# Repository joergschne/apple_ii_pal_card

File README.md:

# apple_ii_pal_card
 Apple II PAL Card - reloaded

APPLE II forever!

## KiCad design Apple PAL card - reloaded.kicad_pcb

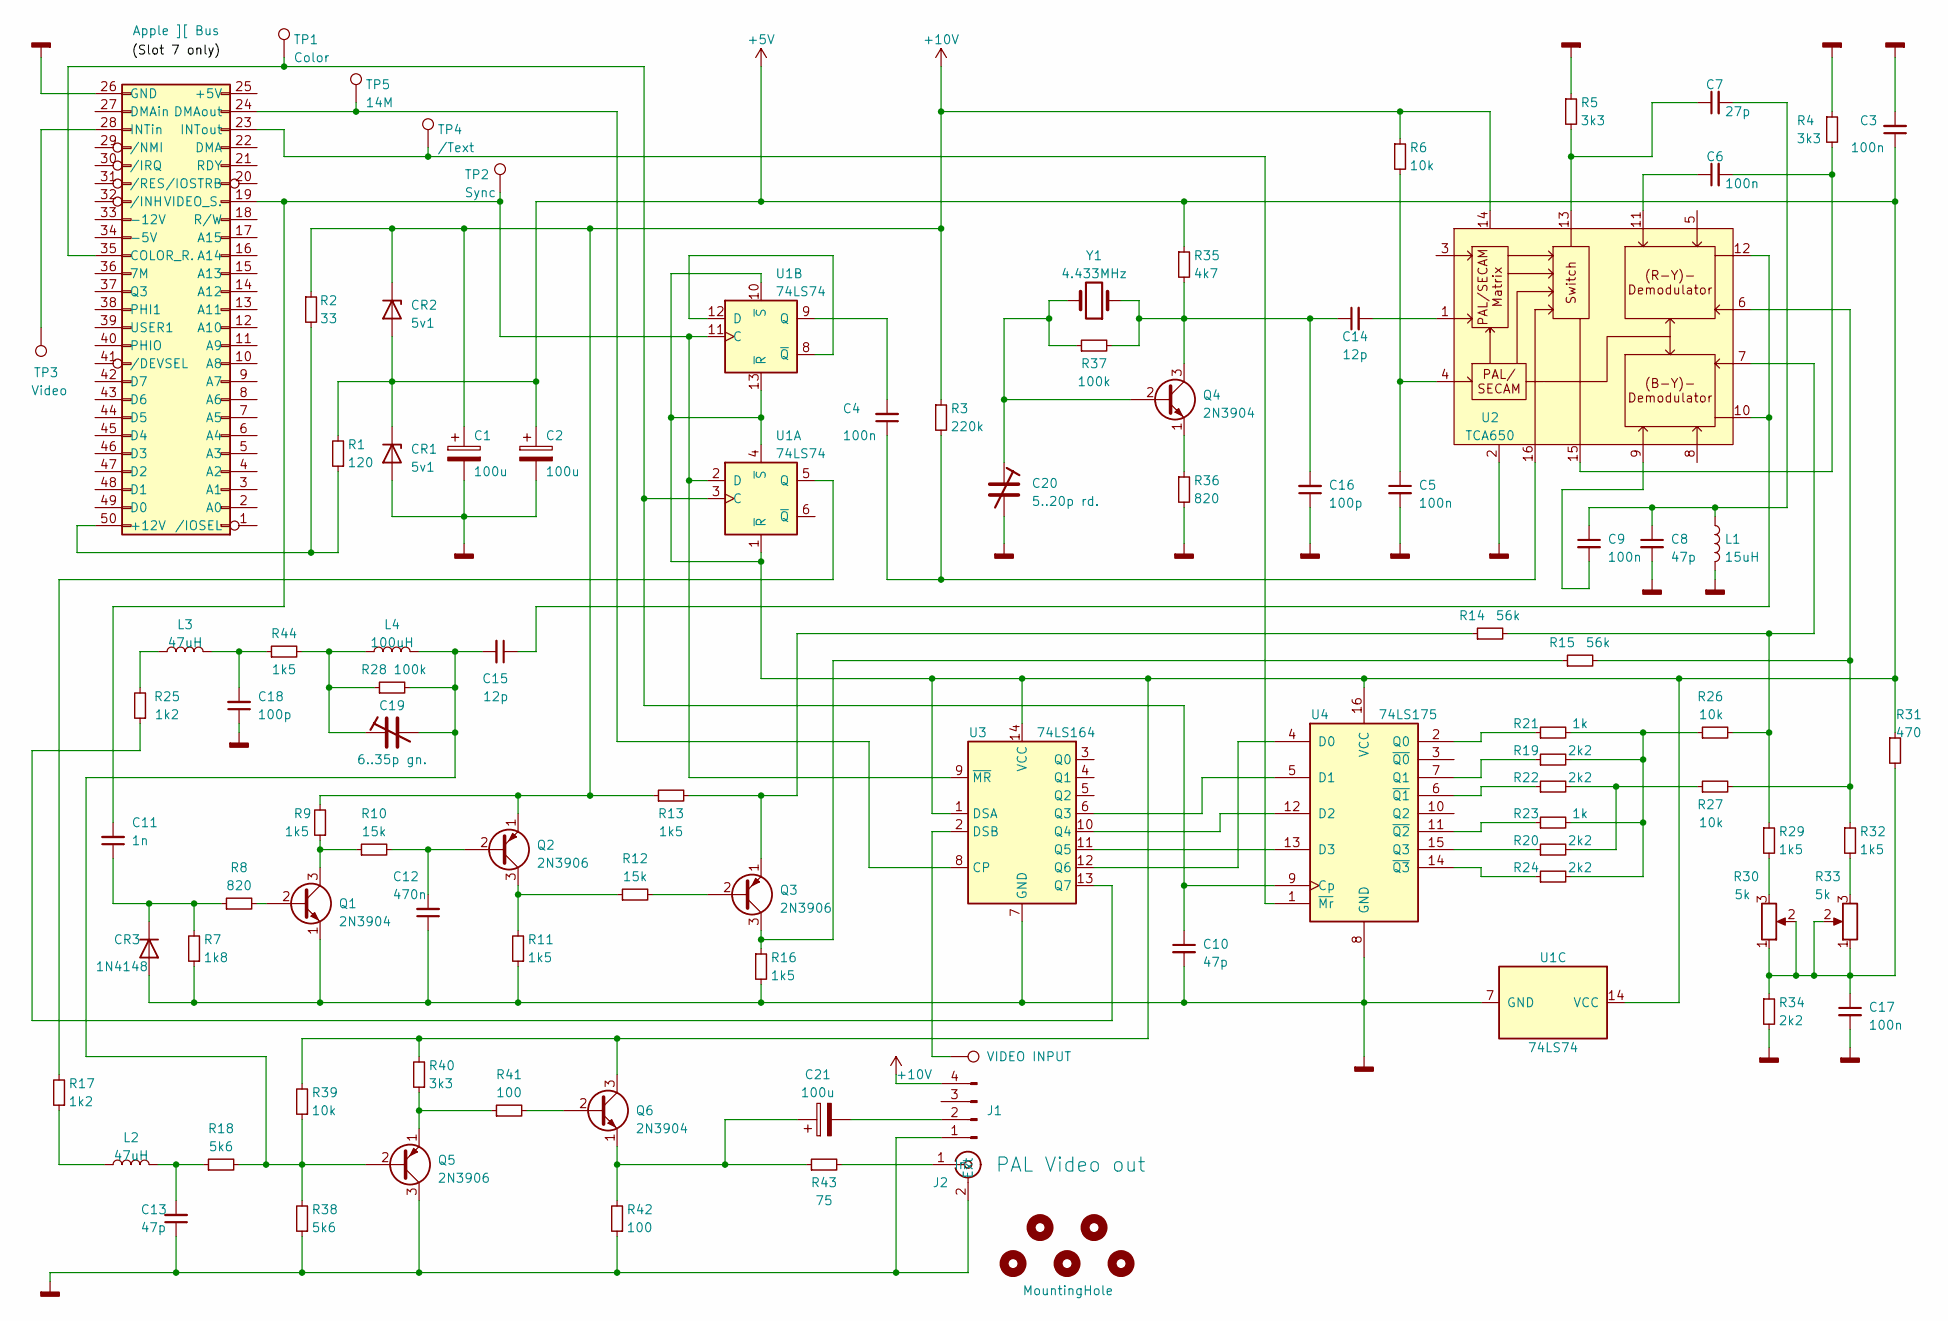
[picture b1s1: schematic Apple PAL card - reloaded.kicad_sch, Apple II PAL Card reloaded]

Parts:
C1, C2, C21: 100u; CP_Radial_D8.0mm_P3.50mm
C3, C4, C5, C6, C9, C17: 100n; C_Disc_D4.3mm_W1.9mm_P5.00mm
C7: 27p; C_Disc_D4.3mm_W1.9mm_P5.00mm
C8, C10, C13: 47p; C_Disc_D4.3mm_W1.9mm_P5.00mm
C11: 1n; C_Disc_D4.3mm_W1.9mm_P5.00mm
C12: 470n; C_Disc_D4.3mm_W1.9mm_P5.00mm
C14, C15: 12p; C_Disc_D4.3mm_W1.9mm_P5.00mm
C16, C18: 100p; C_Disc_D4.3mm_W1.9mm_P5.00mm
C19: 6..35p gn.; Trimmer
C20: 5..20p rd.; Trimmer
CR1, CR2: 5v1; D_DO-35_SOD27_P7.62mm_Horizontal
CR3: 1N4148; D_DO-34_SOD68_P7.62mm_Horizontal
H1, H2, H3: MountingHole; MountingHole_2mm
H4, H5: MountingHole; MountingHole_3.2mm_M3
J1: Modulator; PinHeader_1x04_P2.54mm_Vertical
J2: PAL Video out; Cinch
J3: Apple ][ Bus
L1: 15uH; L_Axial_L5.3mm_D2.2mm_P10.16mm_Horizontal_Vishay_IM-1
L2, L3: 47uH; L_Axial_L5.3mm_D2.2mm_P10.16mm_Horizontal_Vishay_IM-1
L4: 100uH; L_Axial_L5.3mm_D2.2mm_P10.16mm_Horizontal_Vishay_IM-1
Q1, Q4, Q6: 2N3904; TO-92
Q2, Q3, Q5: 2N3906; TO-92
R1: 120; R_Axial_DIN0207_L6.3mm_D2.5mm_P15.24mm_Horizontal
R2: 33; R_Axial_DIN0207_L6.3mm_D2.5mm_P15.24mm_Horizontal
R3: 220k; R
R4, R5, R40: 3k3; R
R6, R26, R27, R39: 10k; R
R7: 1k8; R
R8, R36: 820; R
R9, R11, R13, R16, R29, R32, R44: 1k5; R
R10, R12: 15k; R
R14, R15: 56k; R
R17, R25: 1k2; R
R18, R38: 5k6; R
R19, R20, R22, R24, R34: 2k2; R
R21, R23: 1k; R
R28, R37: 100k; R
R30, R33: 5k; Potentiometer_Piher_PT-10-H01_Horizontal
R31: 470; R
R35: 4k7; R
R41, R42: 100; R
R43: 75; R
TP1: Color; TestPoint_THTPad_D2.0mm_Drill1.0mm
TP2: Sync; TestPoint_THTPad_D2.0mm_Drill1.0mm
TP3: Video; TestPoint_THTPad_D2.0mm_Drill1.0mm
TP4: /Text; TestPoint_THTPad_D2.0mm_Drill1.0mm
TP5: 14M; TestPoint_THTPad_D2.0mm_Drill1.0mm
TP6: VIDEO INPUT; TestPoint_THTPad_D2.0mm_Drill1.0mm
U1: 74LS74; DIP-14_W7.62mm_Socket
U2: TCA650; DIP-16_W7.62mm_Socket
U3: 74LS164; DIP-14_W7.62mm_Socket
U4: 74LS175; DIP-16_W7.62mm_Socket
Y1: 4.433MHz; Crystal_HC49-U_Horizontal

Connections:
+5V: C2.1, C3.1, CR1.1 (K), CR2.2 (A), Q6.3 (C), R1.2, R31.1, R35.1, R39.2, R40.2, U1.1 (~R), U1.4 (~S), U1.10 (~S), U1.13 (~R), U1.14 (VCC), U3.1 (DSA), U3.14 (VCC), U4.16 (VCC)
+10V: C1.1, CR2.1 (K), J1.4, Q2.1 (E), R2.1, R3.1, R6.1, R9.2, R13.1, U2.14
GNDD: C1.2, C2.2, C3.2, C5.2, C8.2, C10.2, C12.1, C13.1, C16.1, C17.2, C18.1, C20.2, CR1.2 (A), CR3.2 (A), J1.1, J2.2 (Ext), J3.26 (GND), L1.2, Q1.1 (E), Q5.3 (C), R4.1, R5.1, R7.1, R11.1, R16.2, R34.2, R36.2, R38.1, R42.1, U1.7 (GND), U2.2, U3.7 (GND), U4.8 (GND)
unnamed: C4.1, R3.2, U2.16
unnamed: C5.1, R6.2, U2.4
unnamed: C6.1, U2.11
unnamed: C6.2, R4.2, U2.15
unnamed: C7.1, R5.2, U2.13
unnamed: C7.2, C8.1, C9.1, L1.1
unnamed: C9.2, U2.9
unnamed: C13.2, L2.2, R18.1
unnamed: C14.2, U2.1
unnamed: C15.1, U2.10, U2.12
unnamed: C17.1, R30.1, R30.2, R31.2, R33.1, R33.2, R34.1
unnamed: C18.2, L3.2, R44.1
unnamed: C19.1, L4.1, R28.1, R44.2
unnamed: C11.1, CR3.1 (K), R7.2, R8.1
unnamed: C21.2, J1.2
unnamed: J2.1 (In), R43.2
unnamed: J3.50 (+12V), R1.1, R2.2
unnamed: C10.1, J3.35 (COLOR_R.), TP1.1, U1.3 (C), U4.9 (Cp)
unnamed: J3.24 (DMAout), TP5.1, U3.8 (CP)
unnamed: J3.28 (INTin), TP3.1
unnamed: J3.23 (INTout), TP4.1, U4.1 (~Mr)
unnamed: C11.2, J3.19 (VIDEO_S.), TP2.1, U1.2 (D), U1.11 (C), U3.9 (~MR)
unnamed: L2.1, R17.1
unnamed: L3.1, R25.2
unnamed: Q1.2 (B), R8.2
unnamed: Q1.3 (C), R9.1, R10.1
unnamed: C12.2, Q2.2 (B), R10.2
unnamed: Q2.3 (C), R11.2, R12.1
unnamed: Q3.2 (B), R12.2
unnamed: Q3.3 (C), R15.1, R16.1
unnamed: Q3.1 (E), R13.2, R14.1
unnamed: C20.1, Q4.2 (B), R37.1, Y1.2
unnamed: C14.1, C16.2, Q4.3 (C), R35.2, R37.2, Y1.1
unnamed: Q4.1 (E), R36.1
unnamed: C15.2, C19.2, L4.2, Q5.2 (B), R18.2, R28.2, R38.2, R39.1
unnamed: Q5.1 (E), R40.1, R41.1
unnamed: Q6.2 (B), R41.2
unnamed: C21.1, Q6.1 (E), R42.2, R43.1
unnamed: R14.2, R26.2, R29.1, U2.7
unnamed: R15.2, R27.2, R32.1, U2.6
unnamed: R19.2, R21.2, R23.2, R24.2, R26.1
unnamed: R20.2, R22.2, R27.1
unnamed: R29.2, R30.3
unnamed: R32.2, R33.3
unnamed: R17.2, U1.5 (Q)
unnamed: U1.8 (~Q), U1.12 (D)
unnamed: C4.2, U1.9 (Q)
unnamed: TP6.1, U3.2 (DSB)
unnamed: U3.6 (Q3), U4.5 (D1)
unnamed: U3.10 (Q4), U4.12 (D2)
unnamed: U3.11 (Q5), U4.13 (D3)
unnamed: U3.12 (Q6), U4.4 (D0)
unnamed: R25.1, U3.13 (Q7)
unnamed: R21.1, U4.2 (Q0)
unnamed: R19.1, U4.7 (Q1)
unnamed: R20.1, U4.15 (Q3)
unnamed: R22.1, U4.6 (~Q1)
unnamed: R23.1, U4.11 (~Q2)
unnamed: R24.1, U4.14 (~Q3)

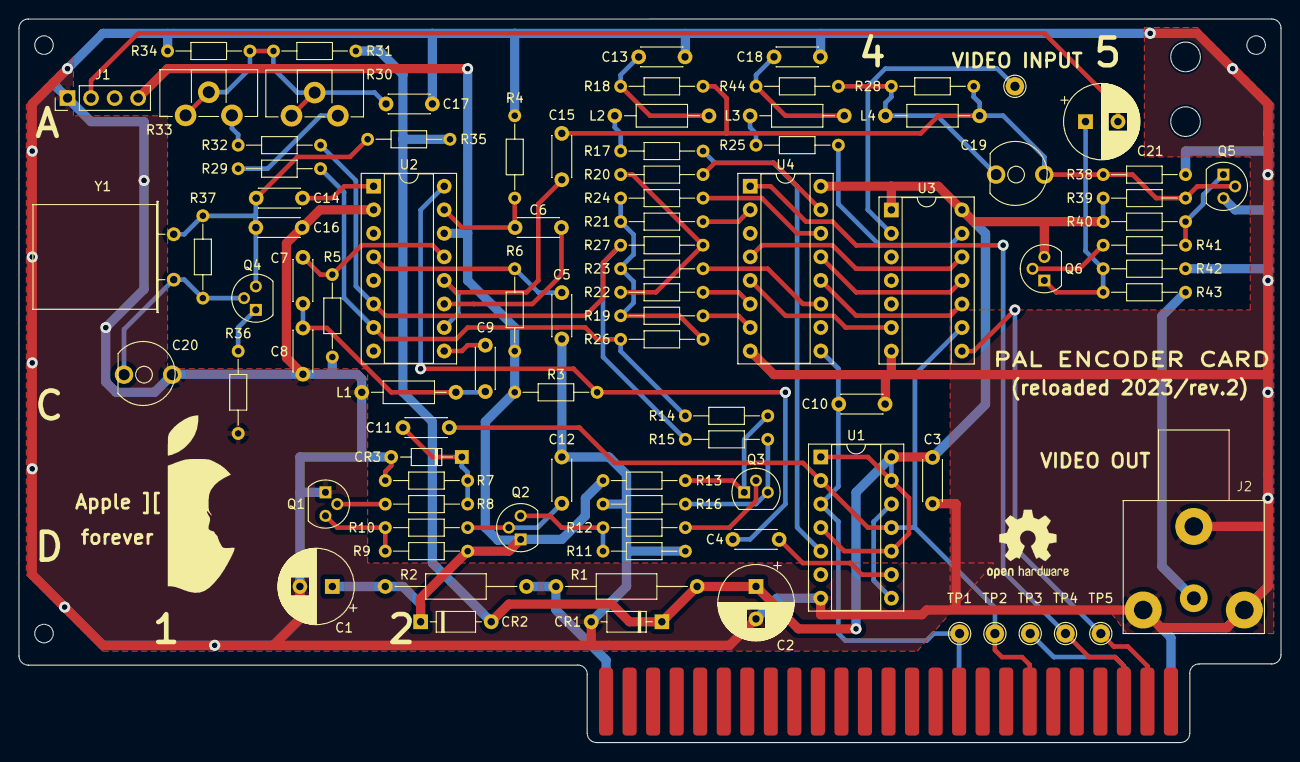
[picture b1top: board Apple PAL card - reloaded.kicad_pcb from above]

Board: 2 copper layers, 136.2 x 78.1 mm, 98 parts (0 on the bottom side), 62 nets.

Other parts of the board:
OSHW Logo: OSHW-Logo2_9.8x8mm_SilkScreen
